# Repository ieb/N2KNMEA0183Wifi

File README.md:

# N2K / NMEA0183 WiFi + BLE bridge

ESP32-C3 firmware that bridges an NMEA2000 (CAN) bus to WiFi and Bluetooth LE
clients. Parses a working subset of N2K PGNs, emits NMEA0183 and SeaSmart over
TCP/UDP/HTTP streams, serves a local web UI and admin, and publishes a
compact binary boat-state feed over BLE GATT for mobile PWAs.

Also bridges a JBD / JDB BMS over TTL/UART, exposing register data both as
custom PGNs on the N2K bus and as a dedicated BLE battery characteristic.

## Features

* NMEA2000 CAN node — parse + emit, built on top of the NMEA2000 library.
* NMEA0183 generation from N2K PGNs (see `lib/N2KHandler/NMEA0183N2KMessages.h`).
* TCP server on port 10110, UDP broadcast, and long-lived chunked HTTP streams
  (`/api/nmea0183`, `/api/seasmart`) with per-client PGN filtering.
* SeaSmart (PCDIN) passthrough with filter negotiation.
* BLE GATT server (`BoatWatchBLE`) — see `docs/ble-transport.md`:
  * `0xAA00` service — autopilot state, command channel, battery.
  * `0xFF00` service — navigation state (lat/lon, COG/SOG, heading, wind,
    depth, STW, log) and engine state (RPM, temps, volts, pressures, hours,
    status bits).
  * PIN-based auth with per-connection and global brute-force lockouts.
  * Fields revert to "not available" sentinels when their source PGN stops
    arriving (≤15 s for nav and slow-cadence engine fields; 5 s for
    engine-running-only fields), so clients don't see stale values.
* JBD BMS bridge over UART — cell voltages, pack V/I/SoC, temps, FET status,
  errors.
* Engine freeze-frame logging to flash (`lib/freezeframe`).
* Performance calculations (polar VMG, target boat speed, target wind angle,
  leeway — see `lib/performance`).
* Logbook to SPIFFS (`lib/logbook`).
* HTTP admin interface (config upload, FS operations, reboot, status).
* WiFi station or AP mode, mDNS.

## UIs

The UIs live in their own repos and talk to the firmware over HTTP streams
or BLE:

* [N2KBMSFwUi](https://github.com/ieb/N2KBMSFwUi) — read-only SPIFFS-hosted UI
  for mobile browsers.
* [N2KUi](https://github.com/ieb/N2KUi) — installable PWA with admin.
* [N2KLifePo4](https://github.com/ieb/N2KLifePo4) — installable PWA for the
  LiFePO4 BMS (BLE).
* [NMEA2000_Booklet](https://github.com/ieb/NMEA2000_Booklet) — Kindle 4
  booklet for use on deck in sunlight.

## Hardware

Current target is an ESP32-C3 on a custom PCB (see `pcb/`). Brownout
threshold is lowered from the 3.1 V default to 2.8 V to ride out BLE radio
bring-up transients. CAN transceiver, isolated UART to the BMS, LED, and
connectors are documented in the schematic.

<div>

</div>

## HTTP API

All paths marked "admin only" require HTTP basic auth against credentials in
`config.txt`.

| Method | Path | Purpose |
| ------ | ---- | ------- |
| GET  | `/**`              | Static file from SPIFFS (UI bundle). |
| GET  | `/api/store`       | Current store snapshot, CSV. |
| GET  | `/api/devices`     | Devices seen on the N2K bus, text. |
| GET  | `/api/nmea0183`    | Chunked NMEA0183 stream. |
| GET  | `/api/seasmart`    | Chunked SeaSmart stream; `?pgns=...` filters. |
| GET  | `/api/status.json` | Filesystem + heap status. *admin* |
| GET  | `/api/fs.json`     | Filesystem listing. *admin* |
| POST | `/api/fs.json`     | `op=delete` or `op=upload` (multipart). *admin* |
| GET  | `/config.txt`      | Current configuration file. *admin* |
| POST | `/api/reboot.json` | Reboot. *admin* |

Simulators for the HTTP/TCP/BMS side live under `simulator/`.

## TCP / UDP (port 10110)

Emits NMEA0183 sentences by default. A client can switch its session to
SeaSmart by sending a PGN filter request — once switched, the stream stays
in SeaSmart mode for that client. Some noisy PGNs (e.g. Raymarine pilot
updates) are filtered by default to protect bandwidth.

    $PCDCM,1,7,127489,127505,127488,128259,129026,130312,128267*77

UDP is used for broadcast to LAN clients. Note that ChromeOS blocks UDP
broadcast to Android apps running in containers, so the TCP and HTTP stream
paths exist as a workaround.

## BLE

See `docs/ble-transport.md` for the binary frame layouts, magic bytes,
scaling factors, and notification cadence. Characteristics notify at ≤2 Hz
when data changes, and fall back to a 1 Hz keep-alive carrying the latest
values (or NA sentinels if the source PGN has gone stale).

Authentication is a 4-digit PIN (`ble.pin` in `config.txt`). Brute force is
bounded by a per-connection lockout (30 s after 5 failures, disconnect after
10) and a global lockout (5 min after 20 cumulative failures across all
connections). Unauthenticated clients are disconnected after 30 s.

## SeaSmart format reference

SeaSmart/PCDIN sentences published on the NMEA0183 streams:

    $PCDIN,01F119,00000000,0F,2AAF00D1067414FF*59
                                               ^^ checksum
                              ^^^^^^^^^^^^^^^^ data (whole message)
                           ^^ source
                  ^^^^^^^^ hex time
           ^^^^^^ PGN
    ^^^^^^ NMEA0183 id

Hex time decoded as `((parseInt(value,32)/1024)+1262304000)*1000` giving ms
since 1970. Reference: [SeaSmart protocol PDF](http://www.seasmart.net/pdf/SeaSmart_HTTP_Protocol_RevG_043012.pdf).

## Usage

On boot the firmware reads `data/config.txt` from SPIFFS and either joins
the configured WiFi network (station mode) or starts its own AP. Find the
resulting IP, then:

* `http://<ip>/`          — data / status view.
* `http://<ip>/admin.html` — admin view (upload config, reboot).

A serial monitor on the ESP32 gives lower-level diagnostics; press `h<CR>`
for a help screen. The running git SHA is printed with `h`.

## Developing

Project uses PlatformIO. Default environment is `esp32-c3`.

    pio run                                  # build firmware
    pio run -t upload                        # flash firmware
    pio run --target buildfs -e esp32-c3     # build SPIFFS image
    pio run --target uploadfs -e esp32-c3    # flash SPIFFS image
    pio device monitor                       # serial console

The SPIFFS image is populated from `data/`. To repopulate it from the
current UI source, clone the relevant UI repo (for the read-only UI that's
[N2KBMSFwUi](https://github.com/ieb/N2KBMSFwUi)) and run its build script.
Simulators under `simulator/` are Node-based and useful for exercising the
HTTP/TCP/BMS paths without hardware.

## Known limitations / history

* WebSockets were removed — the ESP async WebSocket library crashes when
  more than one client connects and the upstream bug is unfixed. Chunked
  HTTP streams replaced them and are stable under load.
* Earlier PCB revisions carried a BME280, ADS1115, TFT display, touch
  sensors, and an OLED. These are all archived — sensing moved to external
  CAN-based sensors (see CanPressure) and display moved to apps. The
  archived code lives under `lib/archive/`.
* An earlier instability was traced to blocking TCP writes hanging the main
  loop; fixed by moving to an async TCP server. CAN bus loaded to 100 % is
  handled without drops.

## Layout

    src/                 firmware entry point
    lib/
      N2KHandler/        PGN parsing, NMEA0183 emitters, freeze-frame hooks
      bluetooth/         BoatWatch BLE server, engine/nav encoders
      network/           HTTP, TCP, UDP, mDNS, wifi bring-up
      jdbbms/            JBD/JDB BMS UART driver
      performance/       polar-based performance calculations
      logbook/           SPIFFS logbook writer
      freezeframe/       engine event freeze-frame recorder
      config/            config.txt loader
    docs/ble-transport.md   BLE GATT + binary framing spec
    simulator/           Node-based HTTP/TCP/BMS simulators
    pcb/                 board design files
    ui/                  scratch / local UI assets (main UIs are in separate repos)

# BUGS/TODO

* [x] Chromebook and Phone continue to show connection instability. Probably fixed with a 500ppm SCA setting.

## Chromebook and Phone continue to show connection instability. 

Could be the shared WiFi/BLE chips in both devices, but could also be the ESP32 having a 500ppm sleep clock accuracy (SCA). Default with NimBLE seems to be 60ppm. I see 520 connection closed reasons in the ESP32 logs, https://github.com/apache/mynewt-nimble/issues/1777 indicates SCA could be the cause.

Testing over 48h is not conclusive since the WiFi environment is not as challenging with weak signals causing the OS interfer with BLE while prioritising Wifi. However, there seem to be fewer disconnects due to 520, and on that basis I am keeping the 500ppm setting for SCA in this commit.

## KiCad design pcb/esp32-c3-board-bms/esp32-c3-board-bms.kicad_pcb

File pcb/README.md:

# PCBs

There are 2 variant, one for an ESP32 WROOM board and one for ESP32-C3 boards. 2 PCBs for the later one using the 18n pin waveshare module and the other using a generic 16 pin module from ebay.

The BMS serial is isolated with a pair of 6N137s as 0v of the BMS will likely not be 0V of the Canbus due to current flowing from the battery pack.  The device is powered from the canbus which is driven through a TJ1050.  The preferred board is one of the ESP32-C3 boards which are more compact and better designed.

# Gcode generation.

For each board, in KiCad
* generate gerbers for front, back and edge.
* generate 1 drill file with all drills.
* Turn of X2 gerber commands as this creates codes that pcb2gcode wont understand.
* decide on where the mirror line will be, default is X=60, which uses a lot of bed space, sometimes best to use a midpoint on X.
* decide where the alignment holes will be, default is +-10 from the mirror, any y10,80. 4 in total.
* run

        ./createGCode.sh <boardname> <mirrorX> <alignOffsetX>  <alignLowerY> <alignUpperY>
        where:
            boardname is the name of the board
            mirrorX is the X of the mirror line, default 60.
            alignOffsetX is the X distance of alignment holes from the mirror line, default = 10
            alignLowerY is the lower Y position default = 10
            alignUpperY is the upper Y position default = 80

* check the output at https://ncviewer.com/

# Milling

NM grbl 0.9 doesnt process M6 or G81 so both are to be disabled during gcode generation.

* mill the fron side,
* drill alignment
* flip and align
* mill backside
* flip and align
* drill from the frontside

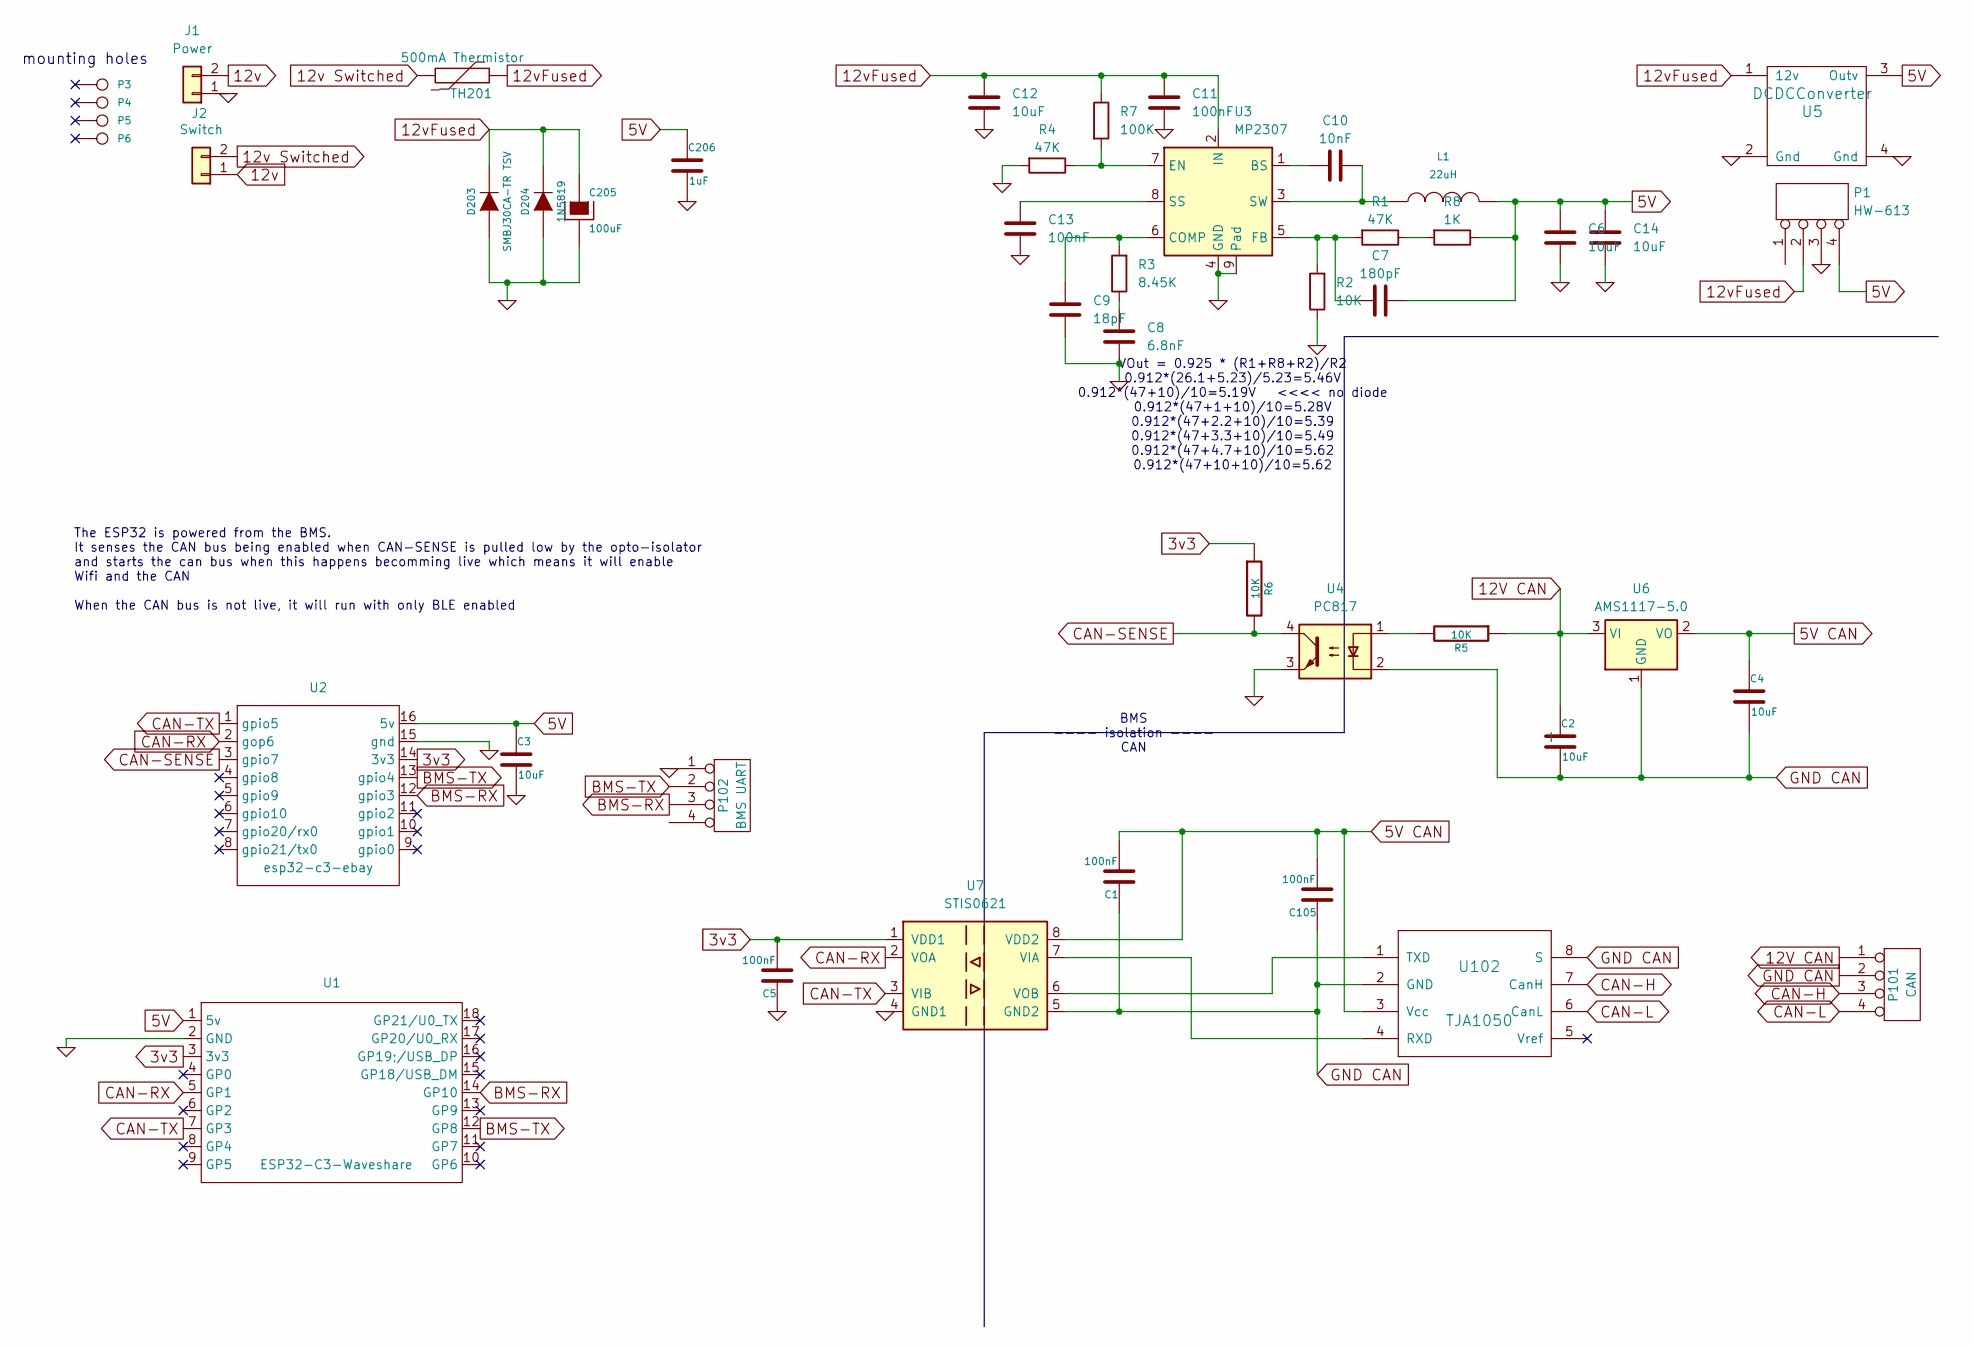
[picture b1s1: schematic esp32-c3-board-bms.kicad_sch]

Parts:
C1, C5, C11, C13, C105: 100nF; C_0805_2012Metric_Pad1.18x1.45mm_HandSolder
C2, C3, C4, C6, C12, C14: 10uF; C_0805_2012Metric_Pad1.18x1.45mm_HandSolder
C7: 180pF; C_0805_2012Metric_Pad1.18x1.45mm_HandSolder
C8: 6.8nF; C_0805_2012Metric_Pad1.18x1.45mm_HandSolder
C9: 18pF; C_0805_2012Metric_Pad1.18x1.45mm_HandSolder
C10: 10nF; C_0805_2012Metric_Pad1.18x1.45mm_HandSolder
C205: 100uF; C_1206_3216Metric_Pad1.33x1.80mm_HandSolder
C206: 1uF; C_1210_3225Metric_Pad1.33x2.70mm_HandSolder
D203: SMBJ30CA-TR TSV; D_SMB_Handsoldering
D204: 1N5819; D_1206_3216Metric_Pad1.42x1.75mm_HandSolder
J1: Power; JST_XH_B2B-XH-A_1x02_P2.50mm_Vertical
J2: Switch; JST_XH_B2B-XH-A_1x02_P2.50mm_Vertical
L1: 22uH; L_APV_ANR6045
P1: HW-613; PinHeader_1x04_P2.54mm_Vertical
P3, P4, P5, P6: CONN_1; MountingHole_3.5mm
P101: CAN; SolderWire-1.5sqmm_1x04_P6mm_D1.7mm_OD3mm
P102: BMS UART; JST_XH_B4B-XH-A_1x04_P2.50mm_Vertical
R1, R4: 47K; R_0805_2012Metric_Pad1.20x1.40mm_HandSolder
R2, R5, R6: 10K; R_0805_2012Metric_Pad1.20x1.40mm_HandSolder
R3: 8.45K; R_0805_2012Metric_Pad1.20x1.40mm_HandSolder
R7: 100K; R_0805_2012Metric_Pad1.20x1.40mm_HandSolder
R8: 1K; R_0805_2012Metric_Pad1.20x1.40mm_HandSolder
TH201: 500mA Thermistor; R_2010_5025Metric_Pad1.40x2.65mm_HandSolder
U1: ESP32-C3-Waveshare; ESP-C3-Zero-Waveshare
U2: esp32-c3-ebay; ESP-C3-Zero-ebay
U3: MP2307; SOIC-8-1EP_3.9x4.9mm_P1.27mm_EP2.62x3.51mm
U4: PC817; DIP-4_W7.62mm
U5: DCDCConverter; Mini360 DCDCConverter
U6: AMS1117-5.0; SOT-223-3_TabPin2
U7: STIS0621; SOIC-8_3.9x4.9mm_P1.27mm
U102: TJA1050; SOIC-8_3.9x4.9mm_P1.27mm

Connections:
3v3: C5.2, R6.1, U1.3 (3v3), U2.14 (3v3), U7.1 (VDD1)
5V CAN: C1.2, C4.1, C105.2, U6.2 (VO), U7.8 (VDD2), U102.3 (Vcc)
12V CAN: C2.1, P101.1, R5.1, U6.3 (VI)
12v: J1.2, J2.1
12v Switched: J2.2, TH201.2
12vFused: C11.1, C12.1, C205.1, D203.2 (K), D204.2 (K), P1.2, R7.1, TH201.1, U3.2 (IN), U5.1 (12v)
BMS-RX: P102.3, U1.14 (GP10), U2.12 (gpio3)
BMS-TX: P102.2, U1.12 (GP8), U2.13 (gpio4)
CAN-H: P101.3, U102.7 (CanH)
CAN-L: P101.4, U102.6 (CanL)
CAN-RX: U1.5 (GP1), U2.2 (gop6), U7.2 (VOA)
CAN-SENSE: R6.2, U2.3 (gpio7), U4.4
CAN-TX: U1.7 (GP3), U2.1 (gpio5), U7.3 (VIB)
GND: C3.2, C5.1, C6.2, C8.1, C9.1, C11.2, C12.2, C13.2, C14.2, C205.2, C206.2, D203.1 (A), D204.1 (A), J1.1, P1.3, P102.1, R2.1, R4.2, U1.2 (GND), U2.15 (gnd), U3.4 (GND), U3.9 (Pad), U4.3, U5.2 (Gnd), U5.4 (Gnd), U7.4 (GND1)
GND CAN: C1.1, C2.2, C4.2, C105.1, P101.2, U4.2, U6.1 (GND), U7.5 (GND2), U102.2 (GND), U102.8 (S)
unnamed: C8.2, R3.1
unnamed: R1.1, R8.2
unnamed: R5.2, U4.1
unnamed: C10.1, U3.1 (BS)
unnamed: C9.2, R3.2, U3.6 (COMP)
unnamed: R4.1, R7.2, U3.7 (EN)
unnamed: C7.1, R1.2, R2.2, U3.5 (FB)
unnamed: C13.1, U3.8 (SS)
unnamed: C10.2, L1.1, U3.3 (SW)
unnamed: U7.7 (VIA), U102.4 (RXD)
unnamed: U7.6 (VOB), U102.1 (TXD)

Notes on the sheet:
VOut = 0.925 * (R1+R8+R2)/R2 0.912*(26.1+5.23)/5.23=5.46V 0.912*(47+10)/10=5.19V <<<< no diode 0.912*(47+1+10)/10=5.28V 0.912*(47+2.2+10)/10=5.39 0.912*(47+3.3+10)/10=5.49 0.912*(47+4.7+10)/10=5.62 0.912*(47+10+10)/10=5.62
BMS ---- isolation ---- CAN
mounting holes
The ESP32 is powered from the BMS. It senses the CAN bus being enabled when CAN-SENSE is pulled low by the opto-isolator and starts the can bus when this happens becomming live which means it will enable Wifi and the CAN When the CAN bus is not live, it will run with only BLE enabled

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
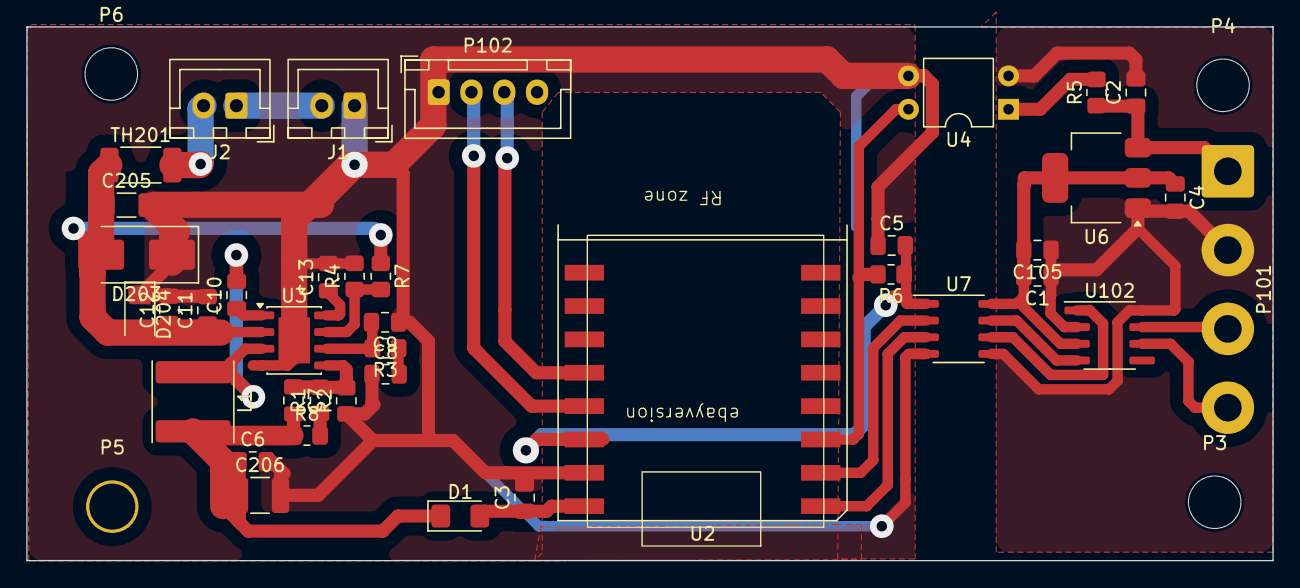
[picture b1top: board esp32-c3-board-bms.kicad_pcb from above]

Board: 2 copper layers, 94.9 x 40.6 mm, 43 parts (0 on the bottom side), 28 nets.

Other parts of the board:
D1: 1N5819; D_1206_3216Metric_Pad1.42x1.75mm_HandSolder

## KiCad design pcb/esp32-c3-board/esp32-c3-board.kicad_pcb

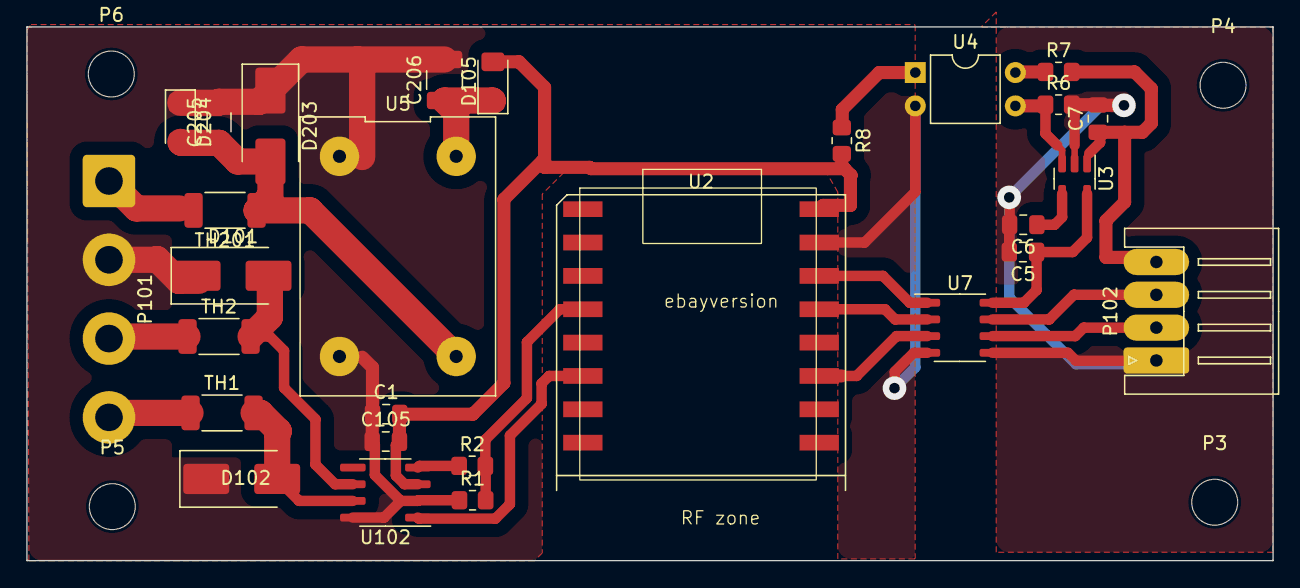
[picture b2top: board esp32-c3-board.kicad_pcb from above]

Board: 2 copper layers, 94.9 x 40.6 mm, 32 parts (0 on the bottom side), 24 nets.

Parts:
C1, C5, C7: 10uF; C_0805_2012Metric_Pad1.18x1.45mm_HandSolder
C6: 10nF; C_0805_2012Metric_Pad1.18x1.45mm_HandSolder
C105: 100nF; C_0805_2012Metric_Pad1.18x1.45mm_HandSolder
C205: 100uF; C_1206_3216Metric_Pad1.33x1.80mm_HandSolder
C206: 1uF; C_1210_3225Metric_Pad1.33x2.70mm_HandSolder
D101, D102, D203: SMBJ30CA-TR TSV; D_SMB_Handsoldering
D105, D204: 1N5819; D_1206_3216Metric_Pad1.42x1.75mm_HandSolder
P3, P4, P5, P6: CONN_1; MountingHole_3.5mm
P101: CAN; SolderWire-1.5sqmm_1x04_P6mm_D1.7mm_OD3mm
P102: BMS UART; JST_XH_S4B-XH-A_1x04_P2.50mm_Horizontal
R1: 3.3K; R_0805_2012Metric_Pad1.20x1.40mm_HandSolder
R2: 2.2K; R_0805_2012Metric_Pad1.20x1.40mm_HandSolder
R6, R8: 10K; R_0805_2012Metric_Pad1.20x1.40mm_HandSolder
R7: 22K; R_0805_2012Metric_Pad1.20x1.40mm_HandSolder
TH1, TH2: Thermistor; R_2010_5025Metric_Pad1.40x2.65mm_HandSolder
TH201: 500mA Thermistor; R_2010_5025Metric_Pad1.40x2.65mm_HandSolder
U2: esp32-c3-ebay; ESP-C3-Zero-ebay
U3: LP2985-3.3; SOT-23-5
U4: PC817; DIP-4_W7.62mm
U5: DCDCConverter; Mini360 DCDCConverter
U7: STIS0621; SOIC-8_3.9x4.9mm_P1.27mm
U102: TJA1050; SOIC-8_3.9x4.9mm_P1.27mm

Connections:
3.3V BMS: C5.1, U3.5 (VOUT), U7.8 (VDD2)
3v3: U2.14 (3v3), U7.1 (VDD1)
5.8V: C206.1, D105.1 (A), U5.3 (Outv)
5V: C1.2, C105.2, D105.2 (K), R8.2, U2.16 (5v), U102.3 (Vcc)
12V BMS: C7.1, P102.4, R7.2, U3.1 (VIN)
12v: P101.1, TH201.2
12vFused: C205.1, D203.2 (K), D204.2 (K), TH201.1, U5.1 (12v)
BMS-RX: U2.13 (gpio4), U7.2 (VOA)
BMS-TX: U2.11 (gpio2), U7.3 (VIB)
CAN-H: P101.4, TH1.1
CAN-L: P101.3, TH2.1
CAN-RX: R1.2, R2.2, U2.4 (gpio8)
CAN-TX: U2.6 (gpio10), U102.1 (TXD)
GND: C1.1, C105.1, C205.2, C206.2, D101.1 (A), D102.1 (A), D203.1 (A), D204.1 (A), P101.2, R1.1, U2.15 (gnd), U4.2, U5.2 (Gnd), U5.4 (Gnd), U7.4 (GND1), U102.2 (GND), U102.8 (S)
GND BMS: C5.2, C6.2, C7.2, P102.1, R6.2, U3.2 (GND), U7.5 (GND2)
unnamed: D101.2 (K), TH2.2, U102.6 (CanL)
unnamed: D102.2 (K), TH1.2, U102.7 (CanH)
unnamed: R7.1, U4.4
unnamed: R8.1, U4.1
unnamed: C6.1, U3.4 (BP)
unnamed: R6.1, U3.3 (ON/~OFF), U4.3
unnamed: R2.1, U102.4 (RXD)
RX from BMS: P102.3, U7.7 (VIA)
TX to BMS: P102.2, U7.6 (VOB)

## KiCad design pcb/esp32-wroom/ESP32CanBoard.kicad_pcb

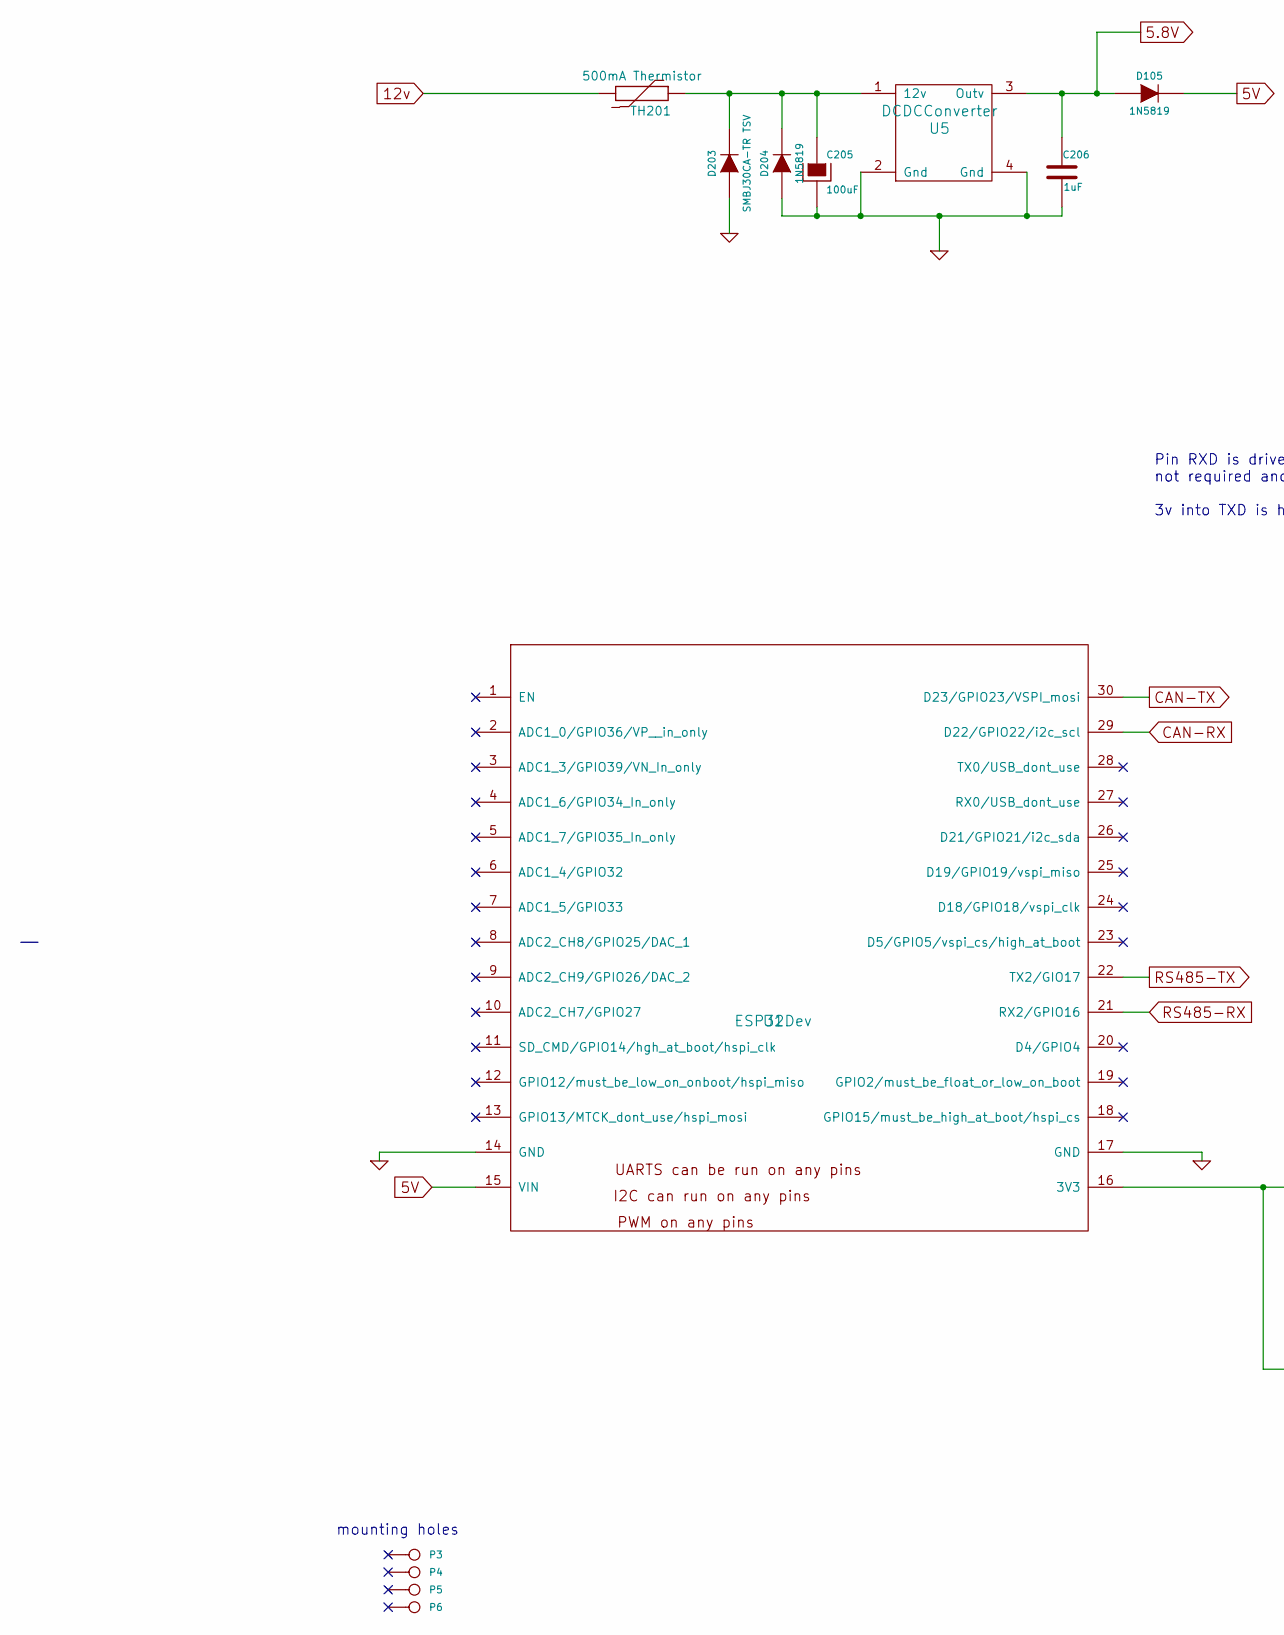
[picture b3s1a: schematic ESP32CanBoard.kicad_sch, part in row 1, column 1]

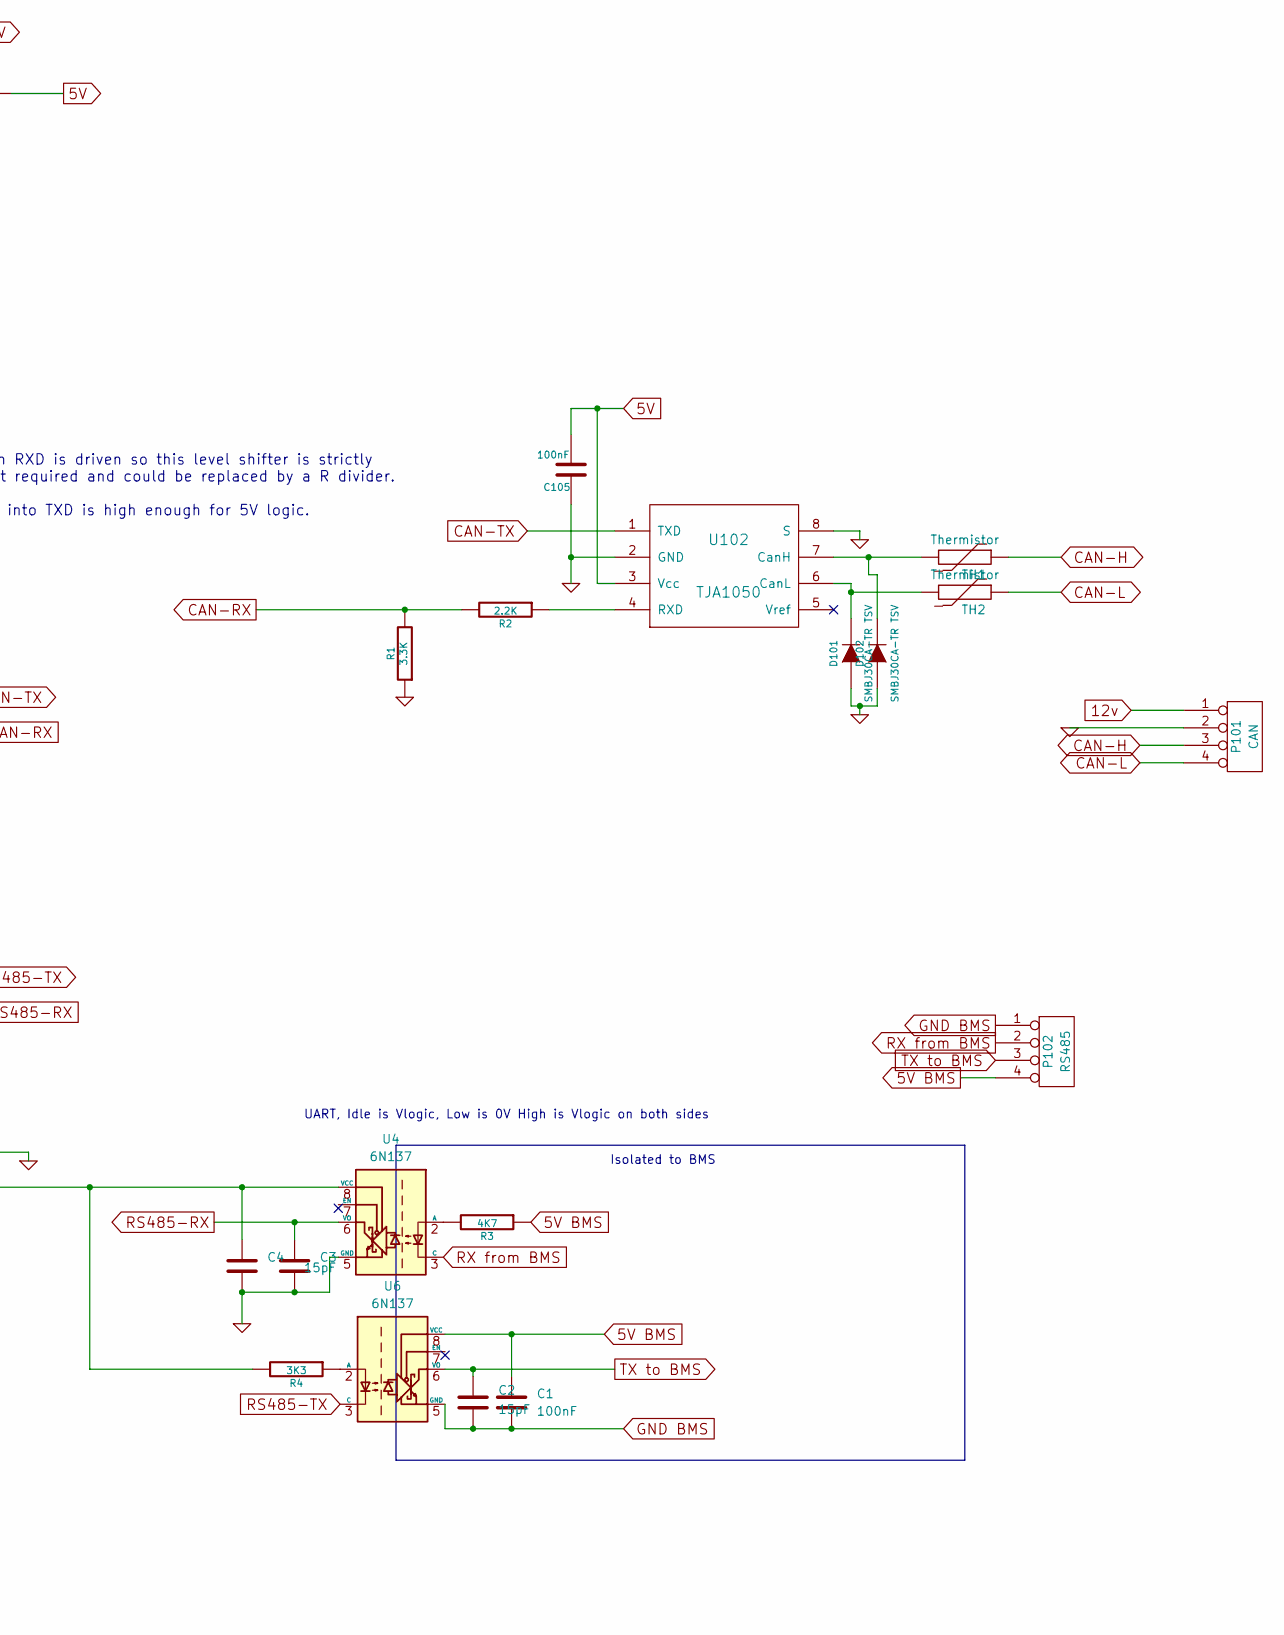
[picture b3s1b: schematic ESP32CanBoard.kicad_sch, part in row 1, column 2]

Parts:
C1, C4, C105: 100nF; C_0805_2012Metric_Pad1.18x1.45mm_HandSolder
C2, C3: 15pF; C_0805_2012Metric_Pad1.18x1.45mm_HandSolder
C205: 100uF; C_1206_3216Metric_Pad1.33x1.80mm_HandSolder
C206: 1uF; C_1210_3225Metric_Pad1.33x2.70mm_HandSolder
D101, D102, D203: SMBJ30CA-TR TSV; DO-214AB
D105, D204: 1N5819; D_1206
P3, P4, P5, P6: CONN_1; 1pin
P101: CAN; bornier4
P102: RS485; JST_XH_S4B-XH-A_1x04_P2.50mm_Horizontal
R1: 3.3K; R_0805_2012Metric_Pad1.20x1.40mm_HandSolder
R2: 2.2K; R_0805_2012Metric_Pad1.20x1.40mm_HandSolder
R3: 4K7; R_0805_2012Metric_Pad1.20x1.40mm_HandSolder
R4: 3K3; R_0805_2012Metric_Pad1.20x1.40mm_HandSolder
TH1, TH2: Thermistor; R_2010_5025Metric_Pad1.40x2.65mm_HandSolder
TH201: 500mA Thermistor; Resistor_Horizontal_RM7mm
U1: ESP32Dev
U4, U6: 6N137; DIP-8_W7.62mm
U5: DCDCConverter; DC-DC-Converter
U102: TJA1050; SOIC-8_3.9x4.9mm_Pitch1.27mm

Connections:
5.8V: C206.1, D105.1 (A), U5.3 (Outv)
5V: C105.2, D105.2 (K), U1.15 (VIN), U102.3 (Vcc)
5V BMS: C1.1, P102.4, R3.1, U6.8 (VCC)
12v: P101.1, TH201.2
CAN-H: P101.3, TH1.1
CAN-L: P101.4, TH2.1
CAN-RX: R1.2, R2.2, U1.29 (D22/GPIO22/i2c_scl)
CAN-TX: U1.30 (D23/GPIO23/VSPI_mosi), U102.1 (TXD)
GND: C3.2, C4.2, C105.1, C205.2, C206.2, D101.1 (A), D102.1 (A), D203.1 (A), D204.1 (A), P101.2, R1.1, U1.14 (GND), U1.17 (GND), U4.5 (GND), U5.2 (Gnd), U5.4 (Gnd), U102.2 (GND), U102.8 (S)
GND BMS: C1.2, C2.2, P102.1, U6.5 (GND)
unnamed: D101.2 (K), TH2.2, U102.6 (CanL)
unnamed: D102.2 (K), TH1.2, U102.7 (CanH)
unnamed: C205.1, D203.2 (K), D204.2 (K), TH201.1, U5.1 (12v)
unnamed: C4.1, R4.2, U1.16 (3V3), U4.8 (VCC)
unnamed: R3.2, U4.2 (A)
unnamed: R4.1, U6.2 (A)
unnamed: R2.1, U102.4 (RXD)
RS485-RX: C3.1, U1.21 (RX2/GPIO16), U4.6 (VO)
RS485-TX: U1.22 (TX2/GIO17), U6.3 (C)
RX from BMS: P102.2, U4.3 (C)
TX to BMS: C2.1, P102.3, U6.6 (VO)

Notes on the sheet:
Pin RXD is driven so this level shifter is strictly not required and could be replaced by a R divider. 3v into TXD is high enough for 5V logic.
mounting holes
Isolated to BMS
UART, Idle is Vlogic, Low is 0V High is Vlogic on both sides

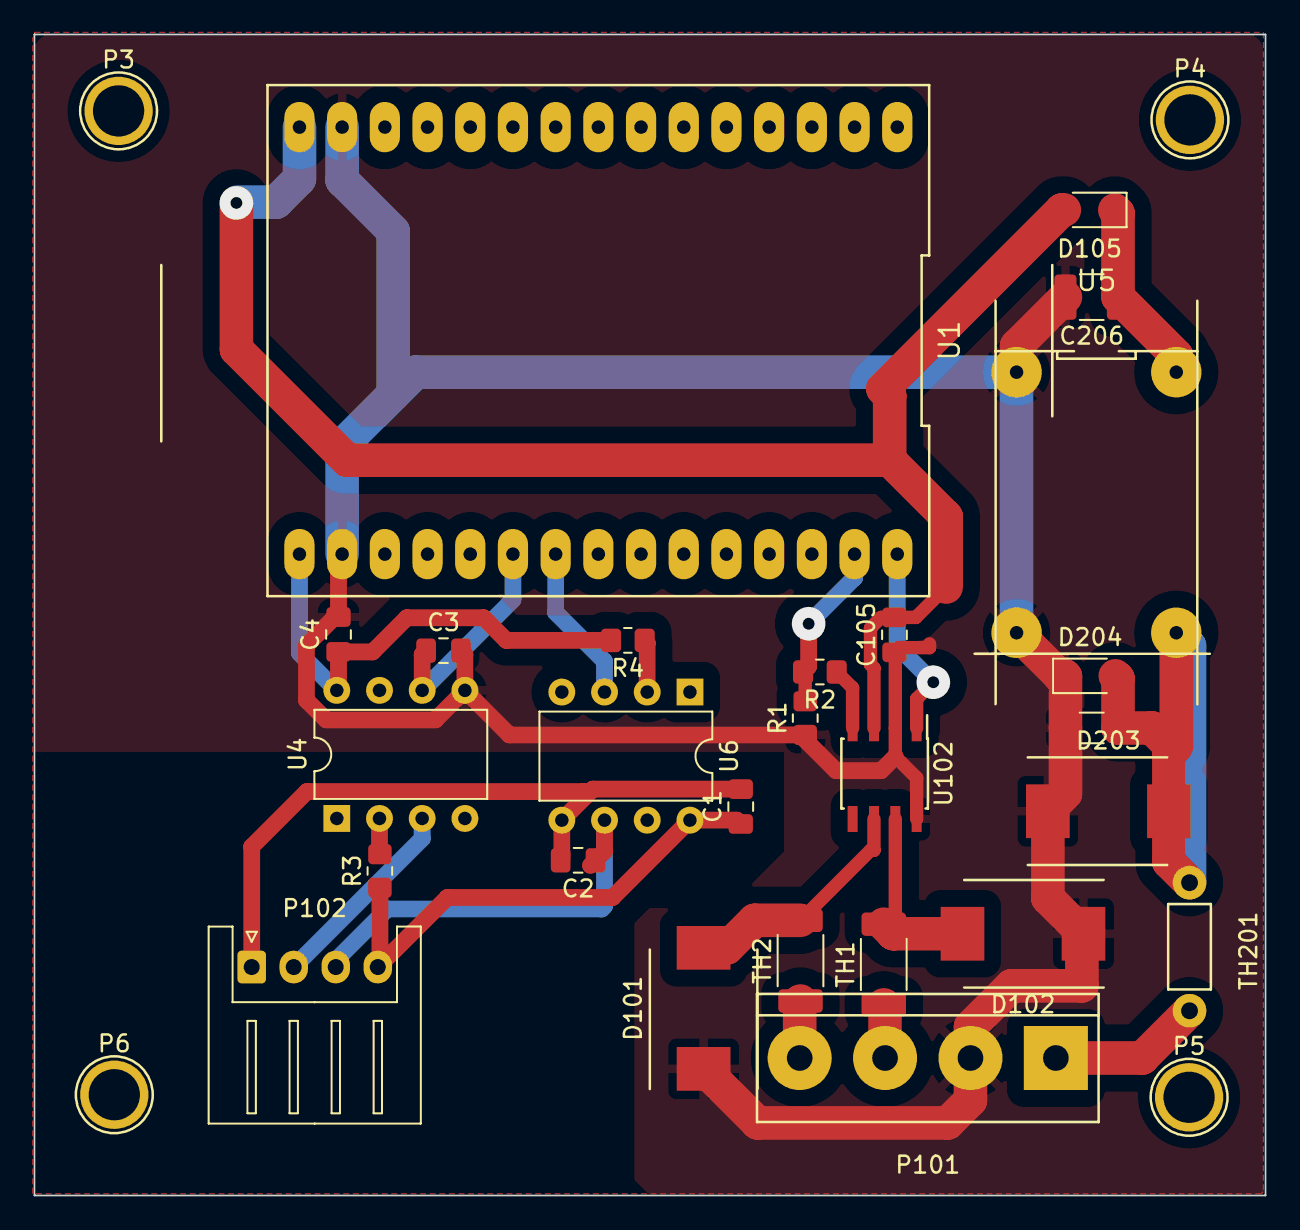
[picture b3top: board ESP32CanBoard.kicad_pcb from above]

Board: 2 copper layers, 73.2 x 69.1 mm, 30 parts (0 on the bottom side), 21 nets.

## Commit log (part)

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2024-04-06 Working version tested with apps
2024-04-06 Removed old pcb files
2024-04-06 Added UDP and WebSocket servers
2024-04-07 Added performance calc output
2024-04-08 Added pgn output on websockets with filtering
2024-04-12 cpp checks cleaned
2024-04-20 Integrating new UI
2024-04-21 V2 UI operational, some bugs remain
2024-04-23 Replaced LazyLog, app now 25KB down from 400KB
2024-04-23 storeview styling
2024-04-23 message viewers working ok
2024-04-29 Added an admin interface for the device filesystem
2024-04-29 Added main menu
2024-04-29 Updated doc
2024-04-29 eink part ported. preact ui mostly done with screenshots
2024-05-02 Added a frame filter for ws endpoints, and improved packet handling and recovery
2024-05-04 Added support for layouts served from SPIFFS
2024-05-14 big eslint sweep, so picky, + PWA
2024-05-17 Added admin login
2024-05-18 Moved the views into 1 PWA
2024-05-18 Added day and night theme
2024-05-24 Made 2 PWAs work together
2024-06-11 Added a debug view to help quickly diagnose can issues
2024-06-13 Fixed layout, improved menu
2024-06-15 Better layout management, fixed polarbugs
2024-06-15 Added default layouts
2024-06-22 More inteactivity on LifePo4 BMS graphs
2024-06-22 Fixed no display of graphs initially
2024-06-23 Added charge dischage guage
2024-09-18 Updated firmware with SeaSmart streams and some ui work
2024-10-28 Dropped websocket use as the ESPAsyncWebServer implementaton crashes frequently, switched to use chunked streaming over http
2024-10-28 Finished conversion to chunked streams
2024-11-11 Intgrated BMS into module and redesigned boards
2024-11-12 Updated boards and readme
2024-11-16 Working version on esp32C3 firmware
2024-11-18 messed up bms uart connector
2024-11-18 debugging ble adapter
2024-12-17 Added some doc and images
2024-12-20 Updated to use seasmart http stream
2024-12-20 Added git version to firmware
2024-12-20 Fixed BMS UI against real firmware
2024-12-21 Tested and fixed E2E with bms simulator
2024-12-21 Fixed missing bms graphs
2024-12-21 Fixed main ui to use better startup from the bms app
2024-12-22 Fixed some sensors and admin login failure
2024-12-22 Added simpler default UI in the FW
2024-12-22 Fixed soc and capacity graphs
2024-12-22 Fixed dump status message for bms
2024-12-23 Added better device UI, still needs more work
2024-12-23 Added screenshots
2024-12-24 verified https streams handling ok
2024-12-24 Split UIs into their own repos
2025-01-18 Working version connected to real BMS
2025-01-19 Included simulations
2025-02-05 Added standard DNS server to improve lookups
2025-02-08 Fixed directory listing
2025-02-08 Fixed message boundary corruption in bms
2025-06-23 Added faster update for BMS messages and send seasmart via POST
2025-06-27 Added transport for inbound seasmart messages with a pgn filter
2025-07-08 Added engine Freeze frame functoinality
2025-07-11 Fixes to dist
2025-07-16 Updated simulator to handle freeze frames
2025-07-21 Fixed COSR on setving files
2025-08-16 Fixing hangs on TCP ports
2025-08-19 fixes to 0183 sentences and further testing
2025-08-19 Improve stability and reduce network load from 20KB/s per connecton to 2KB/s, ESP32-C3 cant handle much
2026-03-30 Added BoatWatch App support
2026-03-31 Implemented Boatwatch BLE Server
2026-04-01 Fixed logging
2026-04-01 Fixed byte order
2026-04-01 use memcpy now endian is the same
2026-04-02 Fixed state event loop to not each cpu
2026-04-02 Fixed potential concurrency issue in http server
2026-04-04 Fixed some bugs and made it possible to start and stop the network with the device powered from the BMS rather than can bus
2026-04-05 Board redesigned to be isolated from the can rather than bms
2026-04-05 Fixed ble disconnect error
2026-04-05 Fixed address claims into an empty bus
2026-04-07 updated board, ready for fab
2026-04-09 Fixed some errors starting and stoping the network
2026-04-09 Fixed BLE error message
2026-04-10 Upgraded NimBLE to 2.x and enabled multiple BLE clients
2026-04-12 Added support for basic nav data over BLE, used by NMEA Bridge app
2026-04-12 Fixed advertising bug
2026-04-12 Fixed min interval update and deprecations
2026-04-16 simulate temps and errors and increase update time
2026-04-18 New case and fixed bootloop
2026-04-19 Added test method for derived values
2026-04-19 Fixed strid 18 bug in polar. Thats bug might be everywhere, need to check
2026-04-19 Added an engine characteristic
2026-04-19 Removed binary
2026-04-19 Missed tests
2026-04-20 updated gitignore for kicad tmp files
2026-04-20 Ensured that engine data becomes stale
2026-04-20 Fixed no engine ble messages
2026-04-20 fixed some possible bugs
2026-04-20 Added diagnostics
2026-04-20 Fixed brownouts on ble start hopefully
2026-04-21 Reporting on BMS status
2026-04-21 Fixed network to only come up on command
2026-04-21 Fixed bug in sumulator
2026-04-21 fixed ble command id
2026-04-21 Cleared nav state when no updates
2026-04-22 Updated readme to match code base
2026-04-22 Added ability to bring Can up without voltage for testing
2026-04-22 Revert "Added ability to bring Can up without voltage for testing"
    This reverts commit 78cff7f1a8ab07a4fa78700b39b697a673bc1f74.
2026-04-22 Revert "Added ability to bring Can up without voltage for testing"
    This reverts commit f13b89df9145439b69aa177063b1d98d4b0a8c6c.
2026-04-30 Fixed missing temperature fields
2026-05-04 onboard MP2307 DCDC
2026-05-14 Added IDF build incase the ISR is impacted by flash
2026-05-17 Dropped package lock since its only for runnng locally
2026-06-02 Bump ws from 8.18.0 to 8.20.1 in /simulator
    Bumps [ws](https://github.com/websockets/ws) from 8.18.0 to 8.20.1.
    - [Release notes](https://github.com/websockets/ws/releases)
    - [Commits](https://github.com/websockets/ws/compare/8.18.0...8.20.1)
    ---
    updated-dependencies:
    - dependency-name: ws
2026-06-16 Integrated FlowMetering
2026-06-17 Moved flowmeter into engine data
2026-06-17 Fixed protocol mismatches and documentaiton bugs
2026-06-17 Example file
2026-06-23 Removing Flowmeter as no longer required
2026-06-29 Disabling logging by default as this is now over BLE
2026-06-29 fixed ws
